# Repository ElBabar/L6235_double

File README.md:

# L6235_double
KiCad double L6235 brushless driver board, with mounted nucleo.

Rackable board for my Robotics club robot, taking part in the Coupe de France de Robotique.

BOM is to come.

You might need to use my library:
add https://github.com/ElBabar/Libabar.git
to your KiCad paths.

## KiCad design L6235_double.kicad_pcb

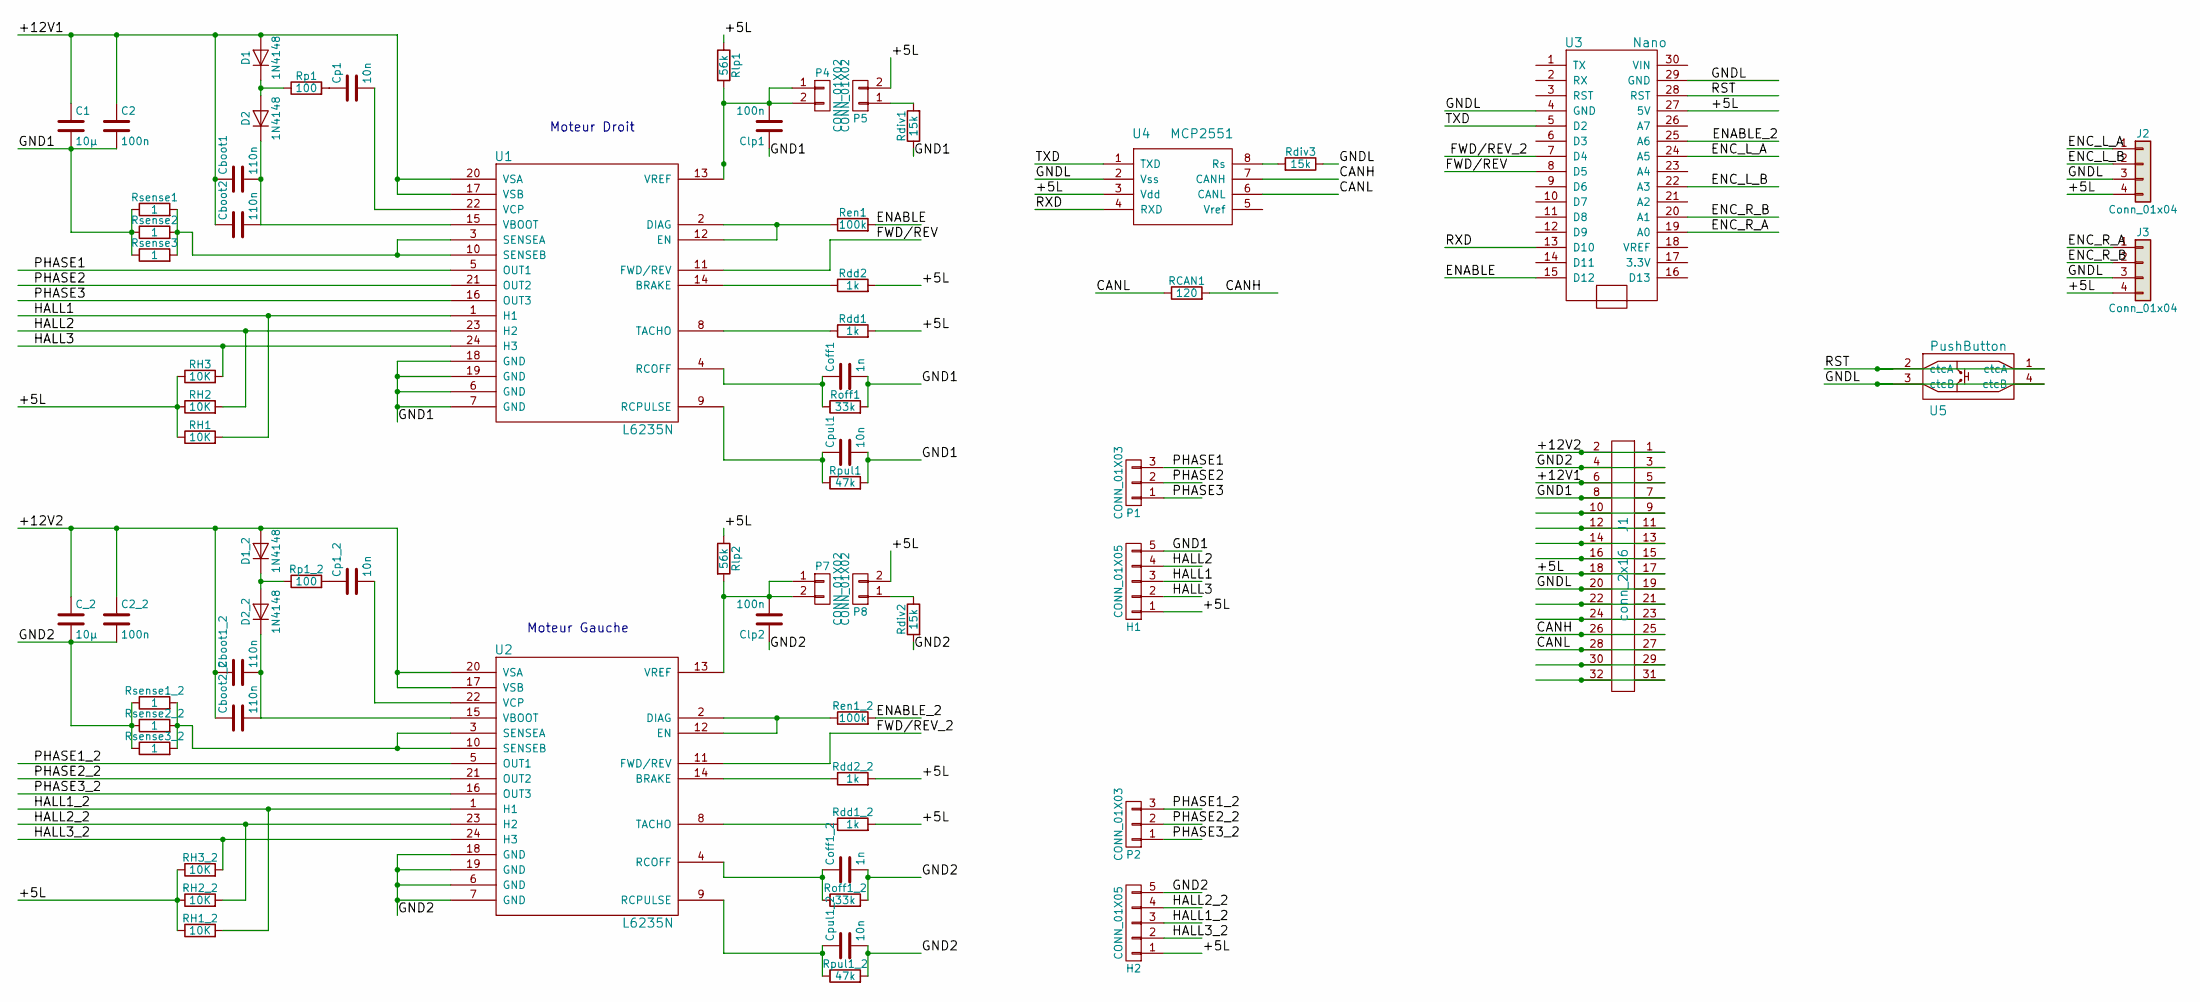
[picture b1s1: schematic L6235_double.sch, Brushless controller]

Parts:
C1: 10µ; CP_Radial_D5.0mm_P2.50mm
C2, C2_2: 100n; C_Disc_D3.8mm_W2.6mm_P2.50mm
C_2: 10µ; CP_Radial_D5.0mm_P2.50mm
Cboot1, Cboot1_2, Cboot2, Cboot2_2: 110n; C_Disc_D3.8mm_W2.6mm_P2.50mm
Clp1, Clp2: 100n; C_Disc_D3.8mm_W2.6mm_P2.50mm
Coff1, Coff1_2: 1n; C_Disc_D3.8mm_W2.6mm_P2.50mm
Cp1, Cp1_2: 10n; C_Disc_D3.8mm_W2.6mm_P2.50mm
Cpul1, Cpul1_2: 10n; C_Disc_D3.8mm_W2.6mm_P2.50mm
D1, D1_2, D2, D2_2: 1N4148; D_A-405_P7.62mm_Horizontal
H1, H2: CONN_01X05; Molex_KK-6410-05_05x2.54mm_Straight
J1: conn_2x16
J2, J3: Conn_01x04; Molex_KK-6410-04_04x2.54mm_Straight
P1, P2: CONN_01X03; Molex_KK-6410-03_03x2.54mm_Straight
P4, P5, P7, P8: CONN_01X02; Pin_Header_Straight_1x02_Pitch2.54mm
RCAN1: 120; R_Axial_DIN0207_L6.3mm_D2.5mm_P7.62mm_Horizontal
RH1, RH1_2, RH2, RH2_2, RH3, RH3_2: 10K; R_Axial_DIN0207_L6.3mm_D2.5mm_P7.62mm_Horizontal
Rdd1, Rdd1_2, Rdd2, Rdd2_2: 1k; R_Axial_DIN0207_L6.3mm_D2.5mm_P7.62mm_Horizontal
Rdiv1, Rdiv2, Rdiv3: 15k; R_Axial_DIN0207_L6.3mm_D2.5mm_P7.62mm_Horizontal
Ren1, Ren1_2: 100k; R_Axial_DIN0207_L6.3mm_D2.5mm_P7.62mm_Horizontal
Rlp1, Rlp2: 56k; R_Axial_DIN0207_L6.3mm_D2.5mm_P7.62mm_Horizontal
Roff1, Roff1_2: 33k; R_Axial_DIN0207_L6.3mm_D2.5mm_P7.62mm_Horizontal
Rp1, Rp1_2: 100; R_Axial_DIN0207_L6.3mm_D2.5mm_P7.62mm_Horizontal
Rpul1, Rpul1_2: 47k; R_Axial_DIN0207_L6.3mm_D2.5mm_P7.62mm_Horizontal
Rsense1, Rsense1_2, Rsense2, Rsense2_2, Rsense3, Rsense3_2: 1; R_Axial_DIN0207_L6.3mm_D2.5mm_P7.62mm_Horizontal
U1, U2: L6235N; PDIP-24
U3: Nano; Nano_STM
U4: MCP2551; PDIP-8
U5: PushButton

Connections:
/+5L: H1.1, H2.1, J1.17, J1.18, J2.4, J3.4, P5.2, P8.2, RH1.1, RH1_2.1, RH2.1, RH2_2.1, RH3.1, RH3_2.1, Rdd1.2, Rdd1_2.2, Rdd2.2, Rdd2_2.2, Rlp1.1, Rlp2.1, U3.27 (5V), U4.3 (Vdd)
/+12V1: C1.1, C2.1, Cboot1.1, Cboot2.1, D1.2 (A), J1.5, J1.6, U1.17 (VSB), U1.20 (VSA)
/+12V2: C2_2.1, C_2.1, Cboot1_2.1, Cboot2_2.1, D1_2.2 (A), J1.1, J1.2, U2.17 (VSB), U2.20 (VSA)
/CANH: J1.25, J1.26, RCAN1.2, U4.7 (CANH)
/CANL: J1.27, J1.28, RCAN1.1, U4.6 (CANL)
/ENABLE: Ren1.2, U3.15 (D12)
/ENABLE_2: Ren1_2.2, U3.25 (A6)
/ENC_L_A: J2.1, U3.24 (A5)
/ENC_L_B: J2.2, U3.22 (A3)
/ENC_R_A: J3.1, U3.19 (A0)
/ENC_R_B: J3.2, U3.20 (A1)
/FWD/REV: U1.11 (FWD/REV), U3.8 (D5)
/FWD/REV_2: U2.11 (FWD/REV), U3.7 (D4)
/GND1: C1.2, C2.2, Clp1.1, Coff1.2, Cpul1.2, H1.5, J1.7, J1.8, Rdiv1.1, Roff1.2, Rpul1.2, Rsense1.1, Rsense2.1, Rsense3.1, U1.6 (GND), U1.7 (GND), U1.18 (GND), U1.19 (GND)
/GND2: C2_2.2, C_2.2, Clp2.1, Coff1_2.2, Cpul1_2.2, H2.5, J1.3, J1.4, Rdiv2.2, Roff1_2.2, Rpul1_2.2, Rsense1_2.1, Rsense2_2.1, Rsense3_2.1, U2.6 (GND), U2.7 (GND), U2.18 (GND), U2.19 (GND)
/GNDL: J1.19, J1.20, J2.3, J3.3, Rdiv3.1, U3.4 (GND), U3.29 (GND), U4.2 (Vss), U5.3 (ctcB), U5.4 (ctcB)
/HALL1: H1.3, RH1.2, U1.1 (H1)
/HALL1_2: H2.3, RH1_2.2, U2.1 (H1)
/HALL2: H1.4, RH2.2, U1.23 (H2)
/HALL2_2: H2.4, RH2_2.2, U2.23 (H2)
/HALL3: H1.2, RH3.2, U1.24 (H3)
/HALL3_2: H2.2, RH3_2.2, U2.24 (H3)
/PHASE1: P1.3, U1.5 (OUT1)
/PHASE1_2: P2.3, U2.5 (OUT1)
/PHASE2: P1.2, U1.21 (OUT2)
/PHASE2_2: P2.2, U2.21 (OUT2)
/PHASE3: P1.1, U1.16 (OUT3)
/PHASE3_2: P2.1, U2.16 (OUT3)
/RST: U3.28 (RST), U5.1 (ctcA), U5.2 (ctcA)
/RXD: U3.13 (D10), U4.4 (RXD)
/TXD: U3.5 (D2), U4.1 (TXD)
unnamed: Cboot1.2, Cboot2.2, D2.1 (K), U1.15 (VBOOT)
unnamed: Cboot1_2.2, Cboot2_2.2, D2_2.1 (K), U2.15 (VBOOT)
unnamed: Clp1.2, P4.1, P4.2, Rlp1.2, U1.13 (VREF)
unnamed: Clp2.2, P7.1, P7.2, Rlp2.2, U2.13 (VREF)
unnamed: Coff1.1, Roff1.1, U1.4 (RCOFF)
unnamed: Coff1_2.1, Roff1_2.1, U2.4 (RCOFF)
unnamed: Cp1.1, Rp1.2
unnamed: Cp1.2, U1.22 (VCP)
unnamed: Cp1_2.1, Rp1_2.2
unnamed: Cp1_2.2, U2.22 (VCP)
unnamed: Cpul1.1, Rpul1.1, U1.9 (RCPULSE)
unnamed: Cpul1_2.1, Rpul1_2.1, U2.9 (RCPULSE)
unnamed: D1.1 (K), D2.2 (A), Rp1.1
unnamed: D1_2.1 (K), D2_2.2 (A), Rp1_2.1
unnamed: J1.9, J1.10
unnamed: J1.11, J1.12
unnamed: J1.13, J1.14
unnamed: J1.15, J1.16
unnamed: J1.21, J1.22
unnamed: J1.23, J1.24
unnamed: J1.29, J1.30
unnamed: J1.31, J1.32
unnamed: P5.1, Rdiv1.2
unnamed: P8.1, Rdiv2.1
unnamed: Rdd1.1, U1.8 (TACHO)
unnamed: Rdd1_2.1, U2.8 (TACHO)
unnamed: Rdd2.1, U1.14 (BRAKE)
unnamed: Rdd2_2.1, U2.14 (BRAKE)
unnamed: Rdiv3.2, U4.8 (Rs)
unnamed: Ren1.1, U1.2 (DIAG), U1.12 (EN)
unnamed: Ren1_2.1, U2.2 (DIAG), U2.12 (EN)
unnamed: Rsense1.2, Rsense2.2, Rsense3.2, U1.3 (SENSEA), U1.10 (SENSEB)
unnamed: Rsense1_2.2, Rsense2_2.2, Rsense3_2.2, U2.3 (SENSEA), U2.10 (SENSEB)

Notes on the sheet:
Moteur Droit
Moteur Gauche

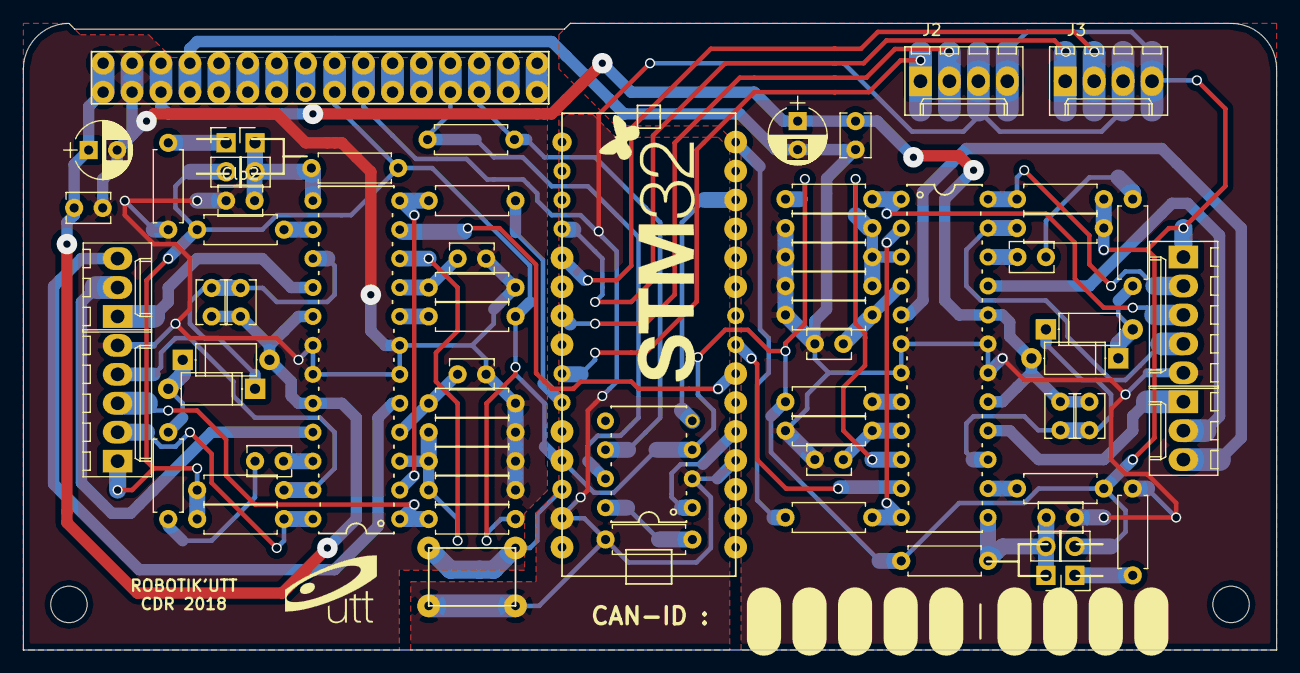
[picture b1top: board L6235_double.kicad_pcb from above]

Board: 2 copper layers, 110.0 x 55.0 mm, 66 parts (0 on the bottom side), 64 nets.

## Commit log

2017-12-08 sending project
2017-12-08 changed Readme
2018-02-07 cosmetic changes
2018-02-07 changed encoder connectors
2018-02-07 generated new gerber
